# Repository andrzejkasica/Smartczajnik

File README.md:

# Smartczajnik
hardware project of smart kettle

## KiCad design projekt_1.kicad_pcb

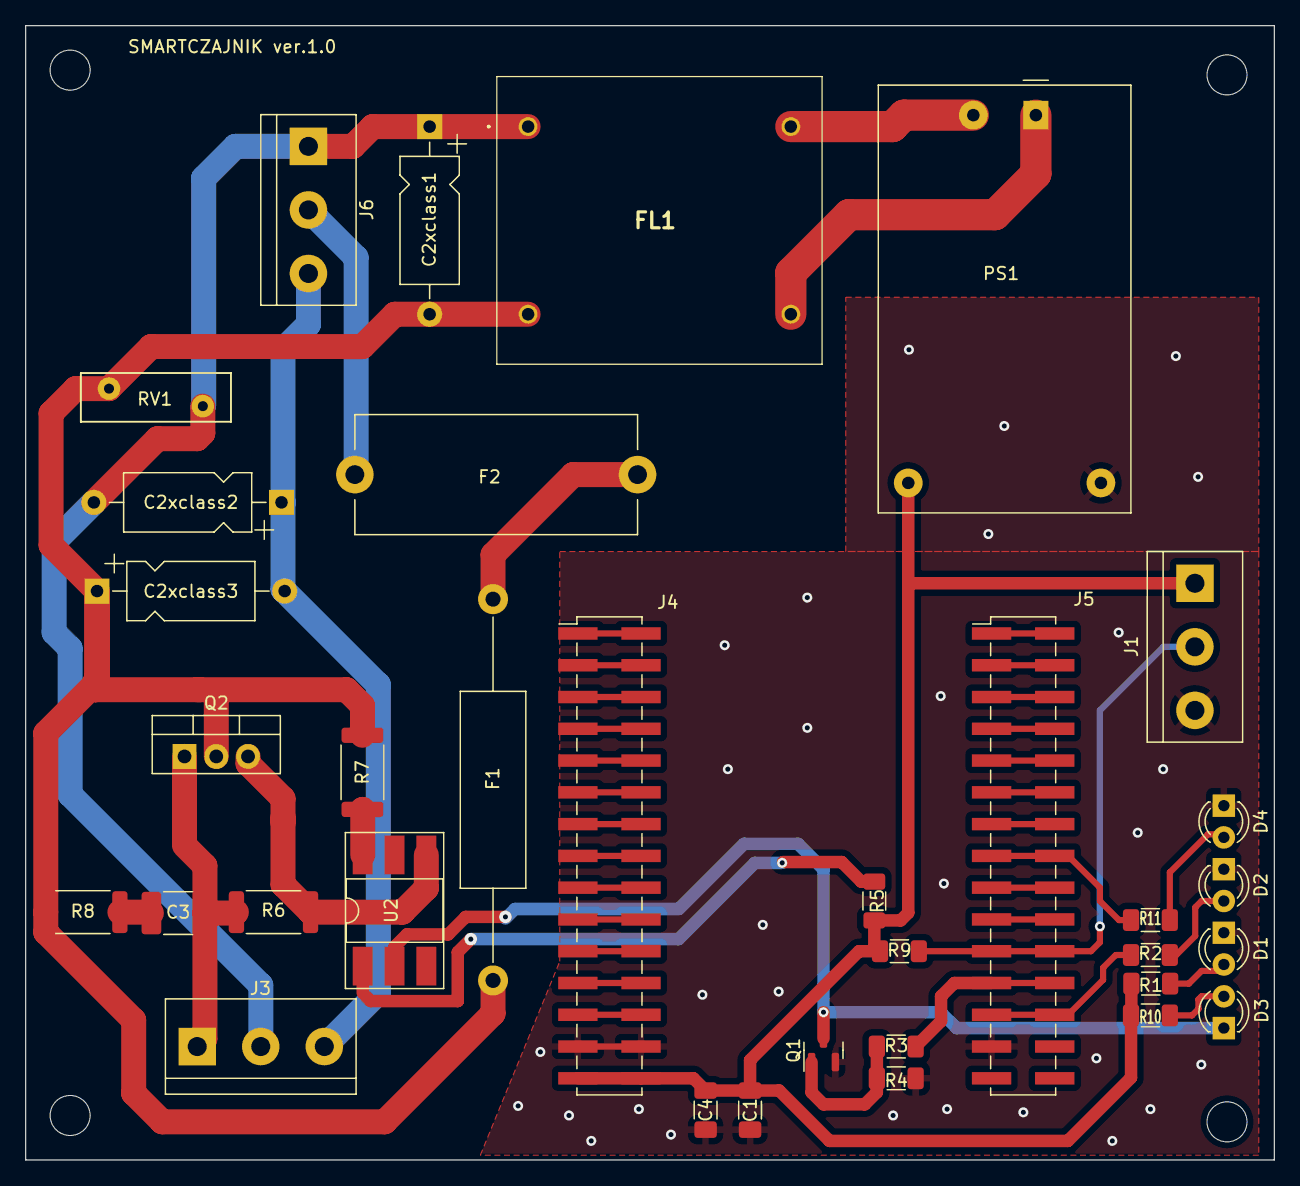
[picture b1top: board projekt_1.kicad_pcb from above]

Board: 2 copper layers, 99.8 x 90.7 mm, 38 parts (0 on the bottom side), 46 nets.

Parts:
C1: 10u; C_1206_3216Metric_Pad1.33x1.80mm_HandSolder
C2xclass1, C2xclass2, C2xclass3: 2.2n; CP_Axial_L10.0mm_D4.5mm_P15.00mm_Horizontal
C3: 22n; C_1812_4532Metric_Pad1.57x3.40mm_HandSolder
C4: 100n; C_1206_3216Metric_Pad1.33x1.80mm_HandSolder
D1: Power On Red LED; LED_D3.0mm
D2: WiFi connected - Green LED; LED_D3.0mm
D3: Heat on - RED LED; LED_D3.0mm
D4: Empty Orange LED; LED_D3.0mm
F1: Thermal Fuse 72 st.; R_Axial_DIN0516_L15.5mm_D5.0mm_P30.48mm_Horizontal
F2: 12.5; Fuseholder_Cylinder-5x20mm_Stelvio-Kontek_PTF78_Horizontal_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
FL1: SSHB21HS-R10300; SSHB21HSR10300
H1, H2, H3, H4: MountingHole; MountingHole_3.2mm_M3
J1: Screw_DS18_Terminal_01x03; TerminalBlock_bornier-3_P5.08mm
J3: Czajnik_plug; TerminalBlock_bornier-3_P5.08mm
J4, J5: Conn_01x15_Female; PinHeader_2x15_P2.54mm_Vertical_SMD
J6: Screw_230v_Terminal_01x03; TerminalBlock_bornier-3_P5.08mm
PS1: HLK-PM01; Converter_ACDC_HiLink_HLK-PMxx
Q1: BSS138; SOT-23
Q2: BTA16-600C; TO-220-3_Vertical
R1, R10: 2.2k; R_1206_3216Metric_Pad1.30x1.75mm_HandSolder
R2: 1,2k; R_1206_3216Metric_Pad1.30x1.75mm_HandSolder
R3: 100; R_1206_3216Metric_Pad1.30x1.75mm_HandSolder
R4: 10k; R_1206_3216Metric_Pad1.30x1.75mm_HandSolder
R5: 390; R_1206_3216Metric_Pad1.30x1.75mm_HandSolder
R6: 330; R_2512_6332Metric
R7: 360; R_2512_6332Metric
R8: 39; R_2512_6332Metric
R9: 4.7k; R_1206_3216Metric_Pad1.30x1.75mm_HandSolder
R11: 1.2k; R_1206_3216Metric_Pad1.30x1.75mm_HandSolder
RV1: Varistor; RV_Disc_D12mm_W3.9mm_P7.5mm
U2: MOC3041M; DIP-6_W8.89mm_SMDSocket_LongPads

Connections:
+3V3: J4.1, J4.16
+5V: C1.1, C4.1, J1.1, J4.15, J4.30, PS1.4 (+Vout), R1.1, R5.2, R9.1, R10.1
/D12: J4.12, J4.27
/D13: J4.13, J4.28
/D14: J4.11, J4.26
/D18?: J5.9, J5.14
/D19: J5.10, J5.12
/D21: J5.10, J5.11
/D22: J5.4, J5.14
/D23: J5.2, J5.15
/D25: J4.8, J4.23
/D26: J4.9, J4.24
/D27: J4.10, J4.25
/D32: J4.6, J4.21
/D33: J4.7, J4.22
/D34: J4.4, J4.19
/D35: J4.5, J4.20
/Drain: D3.1 (K), Q1.3 (D), U2.2
/Empty: J5.8, J5.16, R11.1
/L: C2xclass1.2, C2xclass3.1, F1.1, FL1.2 (N1_2), Q2.2 (A2), R7.1, R8.1, RV1.2
/N: C2xclass1.1, C2xclass2.2, FL1.1 (N1_1), J3.2, J6.1, RV1.1
/OneWire: J1.2, J5.5, J5.22, R9.2
/RX0: J5.8, J5.12
/RX2: J5.6, J5.20
/TX0: J5.6, J5.13
/TX2: J5.7, J5.18
/Triac: J5.4, J5.24, R3.1
/VN: J4.3, J4.18
/VP: J4.2, J4.17
/WiFi_LED: J5.3, J5.26, R2.1
Earth_Protective: C2xclass2.1, C2xclass3.2, J3.3, J6.3
GND: C1.2, C4.2, D1.1 (K), D2.1 (K), D4.1 (K), J1.3, J4.14, J4.29, J5.2, PS1.3 (-Vout), Q1.2 (S), R4.1
unnamed: C3.1, R8.2
unnamed: C3.2, J3.1, Q2.1 (A1), R6.2
unnamed: D1.2 (A), R1.2
unnamed: D2.2 (A), R2.2
unnamed: D3.2 (A), R10.2
unnamed: D4.2 (A), R11.2
unnamed: F1.2, F2.1
unnamed: F2.2, J6.2
unnamed: FL1.3 (N2_1), PS1.1 (AC/L)
unnamed: FL1.4 (N2_2), PS1.2 (AC/N)
unnamed: Q1.1 (G), R3.2, R4.2
unnamed: Q2.3 (G), R6.1, U2.4
unnamed: R5.1, U2.1
unnamed: R7.2, U2.6

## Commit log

2022-04-10 First commit
    a lot to change
2022-05-04 schematic done
